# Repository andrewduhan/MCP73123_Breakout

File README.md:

MCP73123_Breakout
=================

Breakout board for the Microchip MCP73123 LiFePo4 charge controller.

Takes 4V - 16V DC and charges a single LiFePo4 cell at ~3.4V.  
LED will light when charging, turn off when complete.

## BOM:
* MCP73123
* 2x 4.7u ceramic caps (0603)
* 1k resistor (0603)
* LED (1206)
* PROG resistor to set charge current. (0603)  See table in datasheet.

Datasheet:  <a href="http://ww1.microchip.com/downloads/en/DeviceDoc/22191D.pdf">http://ww1.microchip.com/downloads/en/DeviceDoc/22191D.pdf</a>

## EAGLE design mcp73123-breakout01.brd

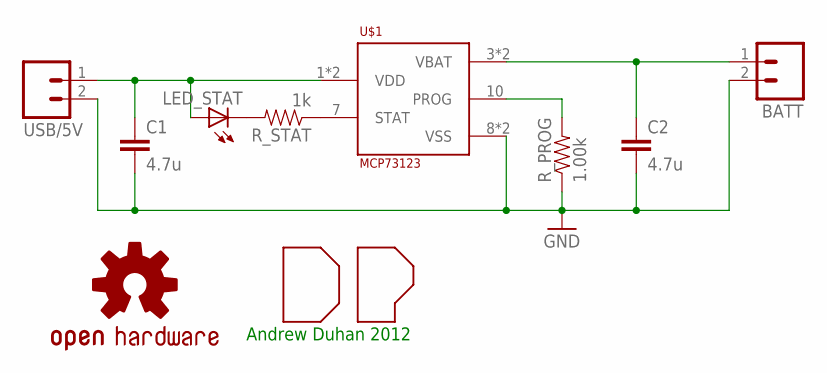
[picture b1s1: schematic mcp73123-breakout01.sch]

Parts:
BATT: M02PTH; 1X02
C1, C2: 4.7u; 0603-CAP
LED_STAT: LED1206; LED-1206
R_PROG: 1.00k; 0603-RES
R_STAT: 1k; 0603-RES
U$1: MCP73123; VDFN10
U$2: DP_LOGO
U$3: OSHW-LOGOS; OSHW-LOGO-S
USB/5V: M02PTH; 1X02

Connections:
GND: BATT.2, C1.2, C2.2, R_PROG.1, U$1.8 (VSS), U$1.9 (VSS), USB/5V.2
unnamed: C1.1, LED_STAT.A, U$1.1 (VDD), U$1.2 (VDD), USB/5V.1
unnamed: R_STAT.1, U$1.7 (STAT)
unnamed: R_PROG.2, U$1.10 (PROG)
unnamed: LED_STAT.C, R_STAT.2
unnamed: BATT.1, C2.1, U$1.3 (VBAT), U$1.4 (VBAT)

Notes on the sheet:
Andrew Duhan 2012

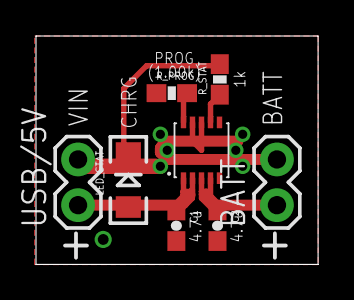
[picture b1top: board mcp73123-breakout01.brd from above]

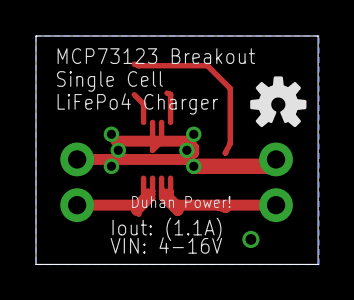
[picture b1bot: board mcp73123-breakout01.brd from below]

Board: 2 copper layers, 15.7 x 12.7 mm, 10 parts (2 on the bottom side), 6 nets.

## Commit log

2012-10-09 aesthetic changes

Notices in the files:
parts and their libraries:
SparkFun-Passives: Licensing: CC v3.0 Share-Alike You are welcome to use this library for commercial purposes.
